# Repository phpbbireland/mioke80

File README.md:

# Moving this repo to phpbbireland/mioke  
The new repo wil correct directory structure for this project... this repo will be deleted...

# mioke80 / ayla_411
QMK Based Open Hardware Keyboard with 99 Keys and Via Support

Just another open source / open hardware ~80% keyboard...

Ref: https://hackaday.io/project/197065-mioke80-iso-99-key-80-keyboard

+ Schematic complete...  
+ Software 80% complete...  
+ QMK/VIA code tested on Blackpill 411 Dev Board (see blackpill_version)... working 11th August 2024
+ Keyboard works... Now loads in usevia.app... Needed work to get RGB and Encoder working...

My main test code is now in /blackpill_version/QMK/ayla/ayla80  

I have designed a new test board using the STM32F411RETx, it contains all the necessary keyboard electronics (except for the key switches, matrix diodes and RGB leds as these are on
the actual keyboard PCB from the first prototype). Connection between boards is via 30 pin 1.27" pitch header connector.  

Note: *kicad2* folder contains working test copy, files will be moved to **kicad** once testing complete...  

Kicad Resources:  
[https://github.com/ebastler/marbastlib](https://github.com/ebastler/marbastlib)  
[https://github.com/joe-scotto/scottokeebs](https://github.com/joe-scotto/scottokeebs)

Matrix 10X10
```
    ┌───┐   ┌───┐┌───┐┌───┬───┬───┬───┐┌───┬───┬───┬───┐┌───┬───┬───┬───┐┌───┐┌───┐┌───┐
    │0,0│   │0,1││N/A││0,2│0,3│0,4│0,5││0,6│0,7│0,8│0,9││1,0│1,1│1,2│1,3││1,4││1,5││1,6│
    └───┘   └───┘└───┘└───┴───┴───┴───┘└───┴───┴───┴───┘└───┴───┴───┴───┘└───┘└───┘└───┘
    ┌───┐   ┌───┬───┬───┬───┬───┬───┬───┬───┬───┬───┬───┬───┬───┬───────┐┌───┐┌───┐┌───┐
    │1,7│   │1,8│1,9│2,0│2,1│2,2│2,3│2,4│2,5│2,6│2,7│2,8│2,9│3,0│  3,1  ││3,2││3,3││3,4│
    ├───┤   ├───┴─┬─┴─┬─┴─┬─┴─┬─┴─┬─┴─┬─┴─┬─┴─┬─┴─┬─┴─┬─┴─┬─┴─┬─┴─┬─────┤├───┤├───┤├───┤
    │3,5│   │ 3,6 │3,7│3,8│3,9│4,0│4,1│4,2│4,3│4,4│4,5│4,6│4,7│4,8│     ││4,9││5,0││5,1│
    ├───┤   ├─────┴┬──┴┬──┴┬──┴┬──┴┬──┴┬──┴┬──┴┬──┴┬──┴┬──┴┬──┴┬──┴┐    │├───┤├───┤├───┤
    │5,2│   │ 5,3  │5,4│5,5│5,6│5,7│5,8│5,9│6,0│6,1│6,2│6,3│6,4│6,5│6.6 ││6,7││6,8││6,9│
    ├───┤   ├────┬─┴─┬─┴─┬─┴─┬─┴─┬─┴─┬─┴─┬─┴─┬─┴─┬─┴─┬─┴─┬─┴─┬─┴───┴────┤├───┤├───┤├───┤
    │7,0│   │7,1 │7,2│7,3│7,4│7,5│7,6│7,7│7,8│7,9│8,0│8,1│8,2│    8,3   ││8,4││8,5││8,6│
    ├───┤   ├────┼───┴┬──┴─┬─┴───┴───┴───┴───┴───┴──┬┴───┼───┴┬────┬────┤├───┤├───┤├───┤
    │8,7│   │8.8 │8,9 │9,1 │           9,2          │9,3 │9,4 │9,5 │9,6 ││9,7││9,8││9,9│
    └───┘   └────┴────┴────┴────────────────────────┴────┴────┴────┴────┘└───┘└───┘└───┘
```

Will add 4x3 number keypad and rotary encoder which attaches via a 5x2 ribbon cable but might need more gpio pin, another process for this version?
The Blackpill version has an endoder... 
**Note**
Some GPIO pins may change as it appears some can't be used (according to sources)...

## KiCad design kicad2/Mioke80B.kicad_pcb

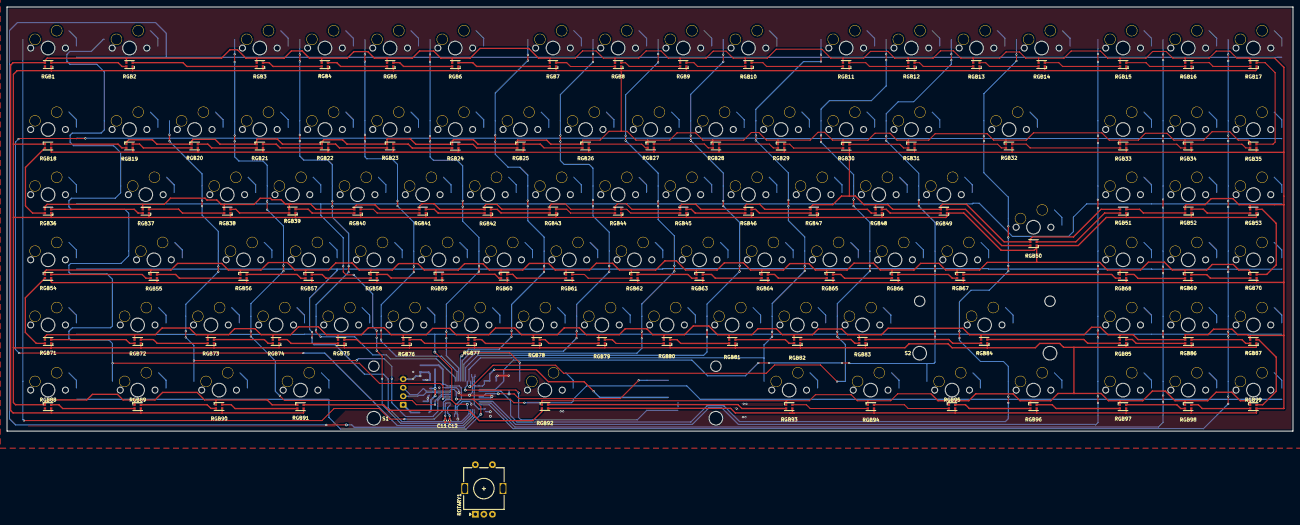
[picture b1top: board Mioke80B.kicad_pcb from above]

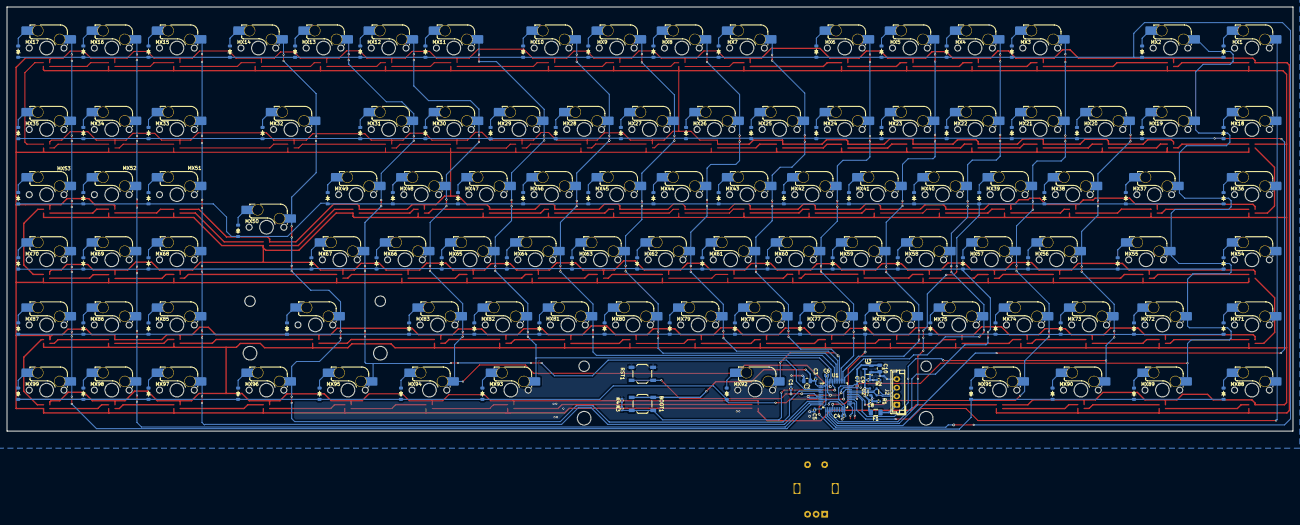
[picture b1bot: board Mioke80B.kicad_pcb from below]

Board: 2 copper layers, 376.0 x 124.0 mm, 323 parts (219 on the bottom side), 236 nets.

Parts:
BOOT1: SW_SPST; SW_SPST_TL3342
C1, C3, C4, C5, C6, C7, C8, C11, C12: 100nF; C_0402_1005Metric
C2: 47uF; C_0805_2012Metric
C9: 1uF; C_0402_1005Metric
C10: 10uF; C_0805_2012Metric
D1, D2, D3, D4, D5, D6, D7, D8, D9, D10, D11, D12, D13, D14, D15, D16, D17, D18, D19, D20, D21, D22, D23, D24, D25, D26, D27, D28, D29, D30, D31, D32, D33, D34, D35, D36, D37, D38, D39, D40, D41, D42, D43, D44, D45, D46, D47, D48, D49, D50, D51, D52, D53, D54, D55, D56, D57, D58, D59, D60, D61, D62, D63, D64, D65, D66, D67, D68, D69, D70, D71, D72, D73, D74, D75, D76, D77, D78, D79, D80, D81, D82, D83, D84, D85, D86, D87, D88, D89, D90, D91, D92, D93, D94, D95, D96, D97, D98, D99: 4148; Diode_SOD-123
F1: 500mA; Fuse_1206_3216Metric
J2: Conn_01x04_Pin; JST_EH_B4B-EH-A_1x04_P2.50mm_Vertical
MX1, MX2, MX3, MX4, MX5, MX6, MX7, MX8, MX9, MX10, MX11, MX12, MX13, MX14, MX15, MX16, MX17, MX18, MX19, MX20, MX21, MX22, MX23, MX24, MX25, MX26, MX27, MX28, MX29, MX30, MX31, MX32, MX33, MX34, MX35, MX36, MX38, MX39, MX40, MX41, MX42, MX43, MX44, MX45, MX46, MX47, MX48, MX49, MX50, MX51, MX52, MX53, MX54, MX56, MX57, MX58, MX59, MX60, MX61, MX62, MX63, MX65, MX66, MX67, MX68, MX69, MX70, MX71, MX73, MX74, MX76, MX77, MX79, MX80, MX82, MX83, MX85, MX86, MX87, MX88, MX92, MX97, MX98, MX99: MX_SW_HS; SW_MX_HS_CPG151101S11_1u
MX37: MX_SW_HS; SW_MX_HS_CPG151101S11_1.5u
MX55, MX64: MX_SW_HS; SW_MX_HS_CPG151101S11_1.75u
MX72, MX89, MX90, MX91, MX93, MX94, MX95, MX96: MX_SW_HS; SW_MX_HS_CPG151101S11_1.25u
MX75, MX78, MX81: MX_SW_HS; SW_MX_HS_1U
MX84: MX_SW_HS; SW_MX_HS_2.75U
R1, R2, R3, R4: 5.1k; R_0402_1005Metric
RGB1, RGB2, RGB3, RGB4, RGB5, RGB6, RGB7, RGB8, RGB9, RGB10, RGB11, RGB12, RGB13, RGB14, RGB15, RGB16, RGB17, RGB18, RGB19, RGB20, RGB21, RGB22, RGB23, RGB24, RGB25, RGB26, RGB27, RGB28, RGB29, RGB30, RGB31, RGB32, RGB33, RGB34, RGB35, RGB36, RGB37, RGB38, RGB39, RGB40, RGB41, RGB42, RGB43, RGB44, RGB45, RGB46, RGB47, RGB48, RGB49, RGB50, RGB51, RGB52, RGB53, RGB54, RGB55, RGB56, RGB57, RGB58, RGB59, RGB60, RGB61, RGB62, RGB63, RGB64, RGB65, RGB66, RGB67, RGB68, RGB69, RGB70, RGB71, RGB72, RGB73, RGB74, RGB75, RGB76, RGB77, RGB78, RGB79, RGB80, RGB81, RGB82, RGB83, RGB84, RGB85, RGB86, RGB87, RGB88, RGB89, RGB90, RGB91, RGB92, RGB93, RGB94, RGB95, RGB96, RGB97, RGB98, RGB99: WS2812B; LED_WS2812B-2020_PLCC4_2.0x2.0mm
ROTARY1: Volume/RGB; RotaryEncoder_Alps_EC11E-Switch_Vertical_H20mm
RST1: SW_SPST; SW_SPST_TL3342
S1: MX_stab; Stabilizer_MX_6.25u
S2: MX_stab; Stabilizer_MX_3.00u
U1: STM32F072CBT6; LQFP-48_7x7mm_P0.5mm
U2: PRTR5V0U2X; SOT-143
U3: XC6206PxxxMR-Regulator_Linear; SOT-23

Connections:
+3V3: BOOT1.1 (A), C2.1, C3.1, C4.1, C5.1, C6.1, C7.1, C10.1, U1.1 (VBAT), U1.9 (VDDA), U1.24 (VDD), U1.36 (VDDIO2), U1.48 (VDD), U3.2 (VO)
+5V: C8.1, C9.1, F1.2, U2.4 (VCC), U3.3 (VI)
BOOT0: BOOT1.2 (B), R3.1, U1.44 (BOOT0)
COL0: MX1.1, MX18.1, MX36.1, MX54.1, MX71.1, MX88.1, U1.28 (PB15)
COL1: MX2.1, MX19.1, MX37.1, MX55.1, MX72.1, MX89.1, U1.29 (PA8)
COL2: MX20.1, MX38.1, MX56.1, MX73.1, MX90.1, U1.30 (PA9)
COL3: MX3.1, MX21.1, MX39.1, MX57.1, MX74.1, MX91.1, U1.31 (PA10)
COL4: MX4.1, MX22.1, MX40.1, MX58.1, MX75.1, U1.37 (PA14)
COL5: MX5.1, MX23.1, MX41.1, MX59.1, MX76.1, U1.38 (PA15)
COL6: MX6.1, MX24.1, MX42.1, MX60.1, MX77.1, U1.39 (PB3)
COL7: MX7.1, MX25.1, MX43.1, MX61.1, MX78.1, MX92.1, U1.40 (PB4)
COL8: MX8.1, MX26.1, MX44.1, MX62.1, MX79.1, U1.41 (PB5)
COL9: MX9.1, MX27.1, MX45.1, MX63.1, MX80.1, U1.42 (PB6)
COL10: MX10.1, MX28.1, MX46.1, MX64.1, MX81.1, U1.43 (PB7)
COL11: MX11.1, MX29.1, MX47.1, MX65.1, MX82.1, MX93.1, U1.45 (PB8)
COL12: MX12.1, MX30.1, MX48.1, MX66.1, MX83.1, MX94.1, U1.46 (PB9)
COL13: MX13.1, MX31.1, MX49.1, MX67.1, MX95.1, U1.3 (PC14)
COL14: MX14.1, MX32.1, MX50.1, MX84.1, MX96.1, U1.4 (PC15)
COL15: MX15.1, MX33.1, MX51.1, MX68.1, MX85.1, MX97.1, U1.10 (PA0)
COL16: MX16.1, MX34.1, MX52.1, MX69.1, MX86.1, MX98.1, U1.11 (PA1)
COL17: MX17.1, MX35.1, MX53.1, MX70.1, MX87.1, MX99.1, U1.12 (PA2)
D+: J2.3, U1.33 (PA12), U2.3 (I/O2)
D-: J2.2, U1.32 (PA11), U2.2 (I/O1)
GND: C1.2, C2.2, C3.2, C4.2, C5.2, C6.2, C7.2, C8.2, C9.2, C10.2, C11.2, C12.2, J2.4, R1.1, R2.2, R4.2, ROTARY1.C, RST1.2 (B), U1.8 (VSSA), U1.23 (VSS), U1.35 (VSS), U1.47 (VSS), U2.1 (GND), U3.1 (GND)
NRST: C1.1, RST1.1 (A), U1.7 (NRST)
unnamed: D1.2 (A), MX1.2
unnamed: D2.2 (A), MX2.2
unnamed: D3.2 (A), MX3.2
unnamed: D4.2 (A), MX4.2
unnamed: D5.2 (A), MX5.2
unnamed: D6.2 (A), MX6.2
unnamed: D7.2 (A), MX7.2
unnamed: D8.2 (A), MX8.2
unnamed: D9.2 (A), MX9.2
unnamed: D10.2 (A), MX10.2
unnamed: D11.2 (A), MX11.2
unnamed: D12.2 (A), MX12.2
unnamed: D13.2 (A), MX13.2
unnamed: D14.2 (A), MX14.2
unnamed: D15.2 (A), MX15.2
unnamed: D16.2 (A), MX16.2
unnamed: D17.2 (A), MX17.2
unnamed: D18.2 (A), MX18.2
unnamed: D19.2 (A), MX19.2
unnamed: D20.2 (A), MX20.2
unnamed: D21.2 (A), MX21.2
unnamed: D22.2 (A), MX22.2
unnamed: D23.2 (A), MX23.2
unnamed: D24.2 (A), MX24.2
unnamed: D25.2 (A), MX25.2
unnamed: D26.2 (A), MX26.2
unnamed: D27.2 (A), MX27.2
unnamed: D28.2 (A), MX28.2
unnamed: D29.2 (A), MX29.2
unnamed: D30.2 (A), MX30.2
unnamed: D31.2 (A), MX31.2
unnamed: D32.2 (A), MX32.2
unnamed: D33.2 (A), MX33.2
unnamed: D34.2 (A), MX34.2
unnamed: D35.2 (A), MX35.2
unnamed: D36.2 (A), MX36.2
unnamed: D37.2 (A), MX37.2
unnamed: D38.2 (A), MX38.2
unnamed: D39.2 (A), MX39.2
unnamed: D40.2 (A), MX40.2
unnamed: D41.2 (A), MX41.2
unnamed: D42.2 (A), MX42.2
unnamed: D43.2 (A), MX43.2
unnamed: D44.2 (A), MX44.2
unnamed: D45.2 (A), MX45.2
unnamed: D46.2 (A), MX46.2
unnamed: D47.2 (A), MX47.2
unnamed: D48.2 (A), MX48.2
unnamed: D49.2 (A), MX49.2
unnamed: D50.2 (A), MX50.2
unnamed: D51.2 (A), MX51.2
unnamed: D52.2 (A), MX52.2
unnamed: D53.2 (A), MX53.2
unnamed: D54.2 (A), MX54.2
unnamed: D55.2 (A), MX55.2
unnamed: D56.2 (A), MX56.2
unnamed: D57.2 (A), MX57.2
unnamed: D58.2 (A), MX58.2
unnamed: D59.2 (A), MX59.2
unnamed: D60.2 (A), MX60.2
unnamed: D61.2 (A), MX61.2
unnamed: D62.2 (A), MX62.2
unnamed: D63.2 (A), MX63.2
unnamed: D64.2 (A), MX64.2
unnamed: D65.2 (A), MX65.2
unnamed: D66.2 (A), MX66.2
unnamed: D67.2 (A), MX67.2
unnamed: D68.2 (A), MX68.2
unnamed: D69.2 (A), MX69.2
unnamed: D70.2 (A), MX70.2
unnamed: D71.2 (A), MX71.2
unnamed: D72.2 (A), MX72.2
unnamed: D73.2 (A), MX73.2
unnamed: D74.2 (A), MX74.2
unnamed: D75.2 (A), MX75.2
unnamed: D76.2 (A), MX76.2
unnamed: D77.2 (A), MX77.2
unnamed: D78.2 (A), MX78.2
unnamed: D79.2 (A), MX79.2
unnamed: D80.2 (A), MX80.2
unnamed: D81.2 (A), MX81.2
unnamed: D82.2 (A), MX82.2
unnamed: D83.2 (A), MX83.2
unnamed: D84.2 (A), MX84.2
unnamed: D85.2 (A), MX85.2
unnamed: D86.2 (A), MX86.2
unnamed: D87.2 (A), MX87.2
unnamed: D88.2 (A), MX88.2
unnamed: D89.2 (A), MX89.2
unnamed: D90.2 (A), MX90.2
unnamed: D91.2 (A), MX91.2
unnamed: D92.2 (A), MX92.2
unnamed: D93.2 (A), MX93.2
unnamed: D94.2 (A), MX94.2
unnamed: D95.2 (A), MX95.2
unnamed: D96.2 (A), MX96.2
unnamed: D97.2 (A), MX97.2
unnamed: D98.2 (A), MX98.2
unnamed: D99.2 (A), MX99.2
unnamed: R3.2, R4.1
unnamed: RGB1.2 (DOUT), RGB2.4 (DIN)
unnamed: RGB1.1 (VDD), RGB2.1 (VDD), RGB3.1 (VDD), RGB4.1 (VDD), RGB5.1 (VDD), RGB6.1 (VDD), RGB7.1 (VDD), RGB8.1 (VDD), RGB9.1 (VDD), RGB10.1 (VDD), RGB11.1 (VDD), RGB12.1 (VDD), RGB13.1 (VDD), RGB14.1 (VDD), RGB15.1 (VDD), RGB16.1 (VDD), RGB17.1 (VDD), RGB18.1 (VDD), RGB19.1 (VDD), RGB20.1 (VDD), RGB21.1 (VDD), RGB22.1 (VDD), RGB23.1 (VDD), RGB24.1 (VDD), RGB25.1 (VDD), RGB26.1 (VDD), RGB27.1 (VDD), RGB28.1 (VDD), RGB29.1 (VDD), RGB30.1 (VDD), RGB31.1 (VDD), RGB32.1 (VDD), RGB33.1 (VDD), RGB34.1 (VDD), RGB35.1 (VDD), RGB36.1 (VDD), RGB37.1 (VDD), RGB38.1 (VDD), RGB39.1 (VDD), RGB40.1 (VDD), RGB41.1 (VDD), RGB42.1 (VDD), RGB43.1 (VDD), RGB44.1 (VDD), RGB45.1 (VDD), RGB46.1 (VDD), RGB47.1 (VDD), RGB48.1 (VDD), RGB49.1 (VDD), RGB50.1 (VDD), RGB51.1 (VDD), RGB52.1 (VDD), RGB53.1 (VDD), RGB54.1 (VDD), RGB55.1 (VDD), RGB56.1 (VDD), RGB57.1 (VDD), RGB58.1 (VDD), RGB59.1 (VDD), RGB60.1 (VDD), RGB61.1 (VDD), RGB62.1 (VDD), RGB63.1 (VDD), RGB64.1 (VDD), RGB65.1 (VDD), RGB66.1 (VDD), RGB67.1 (VDD), RGB68.1 (VDD), RGB69.1 (VDD), RGB70.1 (VDD), RGB71.1 (VDD), RGB72.1 (VDD), RGB73.1 (VDD), RGB74.1 (VDD), RGB75.1 (VDD), RGB76.1 (VDD), RGB77.1 (VDD), RGB78.1 (VDD), RGB79.1 (VDD), RGB80.1 (VDD), RGB81.1 (VDD), RGB82.1 (VDD), RGB83.1 (VDD), RGB84.1 (VDD), RGB85.1 (VDD), RGB86.1 (VDD), RGB87.1 (VDD), RGB88.1 (VDD), RGB89.1 (VDD), RGB90.1 (VDD), RGB91.1 (VDD), RGB92.1 (VDD), RGB93.1 (VDD), RGB94.1 (VDD), RGB95.1 (VDD), RGB96.1 (VDD), RGB97.1 (VDD), RGB98.1 (VDD), RGB99.1 (VDD)
unnamed: RGB1.3 (VSS), RGB2.3 (VSS), RGB3.3 (VSS), RGB4.3 (VSS), RGB5.3 (VSS), RGB6.3 (VSS), RGB7.3 (VSS), RGB8.3 (VSS), RGB9.3 (VSS), RGB10.3 (VSS), RGB11.3 (VSS), RGB12.3 (VSS), RGB13.3 (VSS), RGB14.3 (VSS), RGB15.3 (VSS), RGB16.3 (VSS), RGB17.3 (VSS), RGB18.3 (VSS), RGB19.3 (VSS), RGB20.3 (VSS), RGB21.3 (VSS), RGB22.3 (VSS), RGB23.3 (VSS), RGB24.3 (VSS), RGB25.3 (VSS), RGB26.3 (VSS), RGB27.3 (VSS), RGB28.3 (VSS), RGB29.3 (VSS), RGB30.3 (VSS), RGB31.3 (VSS), RGB32.3 (VSS), RGB33.3 (VSS), RGB34.3 (VSS), RGB35.3 (VSS), RGB36.3 (VSS), RGB37.3 (VSS), RGB38.3 (VSS), RGB39.3 (VSS), RGB40.3 (VSS), RGB41.3 (VSS), RGB42.3 (VSS), RGB43.3 (VSS), RGB44.3 (VSS), RGB45.3 (VSS), RGB46.3 (VSS), RGB47.3 (VSS), RGB48.3 (VSS), RGB49.3 (VSS), RGB50.3 (VSS), RGB51.3 (VSS), RGB52.3 (VSS), RGB53.3 (VSS), RGB54.3 (VSS), RGB55.3 (VSS), RGB56.3 (VSS), RGB57.3 (VSS), RGB58.3 (VSS), RGB59.3 (VSS), RGB60.3 (VSS), RGB61.3 (VSS), RGB62.3 (VSS), RGB63.3 (VSS), RGB64.3 (VSS), RGB65.3 (VSS), RGB66.3 (VSS), RGB67.3 (VSS), RGB68.3 (VSS), RGB69.3 (VSS), RGB70.3 (VSS), RGB71.3 (VSS), RGB72.3 (VSS), RGB73.3 (VSS), RGB74.3 (VSS), RGB75.3 (VSS), RGB76.3 (VSS), RGB77.3 (VSS), RGB78.3 (VSS), RGB79.3 (VSS), RGB80.3 (VSS), RGB81.3 (VSS), RGB82.3 (VSS), RGB83.3 (VSS), RGB84.3 (VSS), RGB85.3 (VSS), RGB86.3 (VSS), RGB87.3 (VSS), RGB88.3 (VSS), RGB89.3 (VSS), RGB90.3 (VSS), RGB91.3 (VSS), RGB92.3 (VSS), RGB93.3 (VSS), RGB94.3 (VSS), RGB95.3 (VSS), RGB96.3 (VSS), RGB97.3 (VSS), RGB98.3 (VSS), RGB99.3 (VSS)
unnamed: RGB2.2 (DOUT), RGB3.4 (DIN)
unnamed: RGB3.2 (DOUT), RGB4.4 (DIN)
unnamed: RGB4.2 (DOUT), RGB5.4 (DIN)
unnamed: RGB5.2 (DOUT), RGB6.4 (DIN)
unnamed: RGB6.2 (DOUT), RGB7.4 (DIN)
unnamed: RGB7.2 (DOUT), RGB8.4 (DIN)
unnamed: RGB8.2 (DOUT), RGB9.4 (DIN)
unnamed: RGB9.2 (DOUT), RGB10.4 (DIN)
unnamed: RGB10.2 (DOUT), RGB11.4 (DIN)
unnamed: RGB11.2 (DOUT), RGB12.4 (DIN)
unnamed: RGB12.2 (DOUT), RGB13.4 (DIN)
unnamed: RGB13.2 (DOUT), RGB14.4 (DIN)
unnamed: RGB14.2 (DOUT), RGB15.4 (DIN)
unnamed: RGB15.2 (DOUT), RGB16.4 (DIN)
unnamed: RGB16.2 (DOUT), RGB17.4 (DIN)
unnamed: RGB17.2 (DOUT), RGB35.4 (DIN)
unnamed: RGB18.4 (DIN), RGB19.2 (DOUT)
unnamed: RGB18.2 (DOUT), RGB36.4 (DIN)
unnamed: RGB19.4 (DIN), RGB20.2 (DOUT)
unnamed: RGB20.4 (DIN), RGB21.2 (DOUT)
unnamed: RGB21.4 (DIN), RGB22.2 (DOUT)
unnamed: RGB22.4 (DIN), RGB23.2 (DOUT)
unnamed: RGB23.4 (DIN), RGB24.2 (DOUT)
unnamed: RGB24.4 (DIN), RGB25.2 (DOUT)
unnamed: RGB25.4 (DIN), RGB26.2 (DOUT)
unnamed: RGB26.4 (DIN), RGB27.2 (DOUT)
unnamed: RGB27.4 (DIN), RGB28.2 (DOUT)
unnamed: RGB28.4 (DIN), RGB29.2 (DOUT)
unnamed: RGB29.4 (DIN), RGB30.2 (DOUT)
unnamed: RGB30.4 (DIN), RGB31.2 (DOUT)
unnamed: RGB31.4 (DIN), RGB32.2 (DOUT)
unnamed: RGB32.4 (DIN), RGB33.2 (DOUT)
unnamed: RGB33.4 (DIN), RGB34.2 (DOUT)
unnamed: RGB34.4 (DIN), RGB35.2 (DOUT)
unnamed: RGB36.2 (DOUT), RGB37.4 (DIN)
unnamed: RGB37.2 (DOUT), RGB38.4 (DIN)
unnamed: RGB38.2 (DOUT), RGB39.4 (DIN)
unnamed: RGB39.2 (DOUT), RGB40.4 (DIN)
unnamed: RGB40.2 (DOUT), RGB41.4 (DIN)
unnamed: RGB41.2 (DOUT), RGB42.4 (DIN)
unnamed: RGB42.2 (DOUT), RGB43.4 (DIN)
unnamed: RGB43.2 (DOUT), RGB44.4 (DIN)
unnamed: RGB44.2 (DOUT), RGB45.4 (DIN)
unnamed: RGB45.2 (DOUT), RGB46.4 (DIN)
unnamed: RGB46.2 (DOUT), RGB47.4 (DIN)
unnamed: RGB47.2 (DOUT), RGB48.4 (DIN)
unnamed: RGB48.2 (DOUT), RGB49.4 (DIN)
unnamed: RGB49.2 (DOUT), RGB50.4 (DIN)
unnamed: RGB50.2 (DOUT), RGB51.4 (DIN)
unnamed: RGB51.2 (DOUT), RGB52.4 (DIN)
unnamed: RGB52.2 (DOUT), RGB53.4 (DIN)
unnamed: RGB53.2 (DOUT), RGB70.4 (DIN)
unnamed: RGB54.4 (DIN), RGB55.2 (DOUT)
unnamed: RGB54.2 (DOUT), RGB71.4 (DIN)
unnamed: RGB55.4 (DIN), RGB56.2 (DOUT)
unnamed: RGB56.4 (DIN), RGB57.2 (DOUT)
unnamed: RGB57.4 (DIN), RGB58.2 (DOUT)
unnamed: RGB58.4 (DIN), RGB59.2 (DOUT)
unnamed: RGB59.4 (DIN), RGB60.2 (DOUT)
unnamed: RGB60.4 (DIN), RGB61.2 (DOUT)
unnamed: RGB61.4 (DIN), RGB62.2 (DOUT)
unnamed: RGB62.4 (DIN), RGB63.2 (DOUT)
unnamed: RGB63.4 (DIN), RGB64.2 (DOUT)
unnamed: RGB64.4 (DIN), RGB65.2 (DOUT)
unnamed: RGB65.4 (DIN), RGB66.2 (DOUT)
unnamed: RGB66.4 (DIN), RGB67.2 (DOUT)
unnamed: RGB67.4 (DIN), RGB68.2 (DOUT)
unnamed: RGB68.4 (DIN), RGB69.2 (DOUT)
unnamed: RGB69.4 (DIN), RGB70.2 (DOUT)
unnamed: RGB71.2 (DOUT), RGB72.4 (DIN)
unnamed: RGB72.2 (DOUT), RGB73.4 (DIN)
unnamed: RGB73.2 (DOUT), RGB74.4 (DIN)
unnamed: RGB74.2 (DOUT), RGB75.4 (DIN)
unnamed: RGB75.2 (DOUT), RGB76.4 (DIN)
unnamed: RGB76.2 (DOUT), RGB77.4 (DIN)
unnamed: RGB77.2 (DOUT), RGB78.4 (DIN)
unnamed: RGB78.2 (DOUT), RGB79.4 (DIN)
unnamed: RGB79.2 (DOUT), RGB80.4 (DIN)
unnamed: RGB80.2 (DOUT), RGB81.4 (DIN)
unnamed: RGB81.2 (DOUT), RGB82.4 (DIN)
unnamed: RGB82.2 (DOUT), RGB83.4 (DIN)
unnamed: RGB83.2 (DOUT), RGB84.4 (DIN)
unnamed: RGB84.2 (DOUT), RGB85.4 (DIN)
unnamed: RGB85.2 (DOUT), RGB86.4 (DIN)
unnamed: RGB86.2 (DOUT), RGB87.4 (DIN)
unnamed: RGB87.2 (DOUT), RGB99.4 (DIN)
unnamed: RGB88.4 (DIN), RGB89.2 (DOUT)
unnamed: RGB89.4 (DIN), RGB90.2 (DOUT)
unnamed: RGB90.4 (DIN), RGB91.2 (DOUT)
unnamed: RGB91.4 (DIN), RGB92.2 (DOUT)
unnamed: RGB92.4 (DIN), RGB93.2 (DOUT)
unnamed: RGB93.4 (DIN), RGB94.2 (DOUT)
unnamed: RGB94.4 (DIN), RGB95.2 (DOUT)
unnamed: RGB95.4 (DIN), RGB96.2 (DOUT)
unnamed: RGB96.4 (DIN), RGB97.2 (DOUT)
unnamed: RGB97.4 (DIN), RGB98.2 (DOUT)
unnamed: RGB98.4 (DIN), RGB99.2 (DOUT)
unnamed: ROTARY1.S1, U1.21 (PB10)
unnamed: ROTARY1.S2, U1.22 (PB11)
unnamed: C12.1, ROTARY1.B, U1.25 (PB12)
unnamed: C11.1, ROTARY1.A, U1.26 (PB13)
ROW0: D1.1 (K), D2.1 (K), D3.1 (K), D4.1 (K), D5.1 (K), D6.1 (K), D7.1 (K), D8.1 (K), D9.1 (K), D10.1 (K), D11.1 (K), D12.1 (K), D13.1 (K), D14.1 (K), D15.1 (K), D16.1 (K), D17.1 (K), U1.13 (PA3)
ROW1: D18.1 (K), D19.1 (K), D20.1 (K), D21.1 (K), D22.1 (K), D23.1 (K), D24.1 (K), D25.1 (K), D26.1 (K), D27.1 (K), D28.1 (K), D29.1 (K), D30.1 (K), D31.1 (K), D32.1 (K), D33.1 (K), D34.1 (K), D35.1 (K), U1.14 (PA4)
ROW2: D36.1 (K), D37.1 (K), D38.1 (K), D39.1 (K), D40.1 (K), D41.1 (K), D42.1 (K), D43.1 (K), D44.1 (K), D45.1 (K), D46.1 (K), D47.1 (K), D48.1 (K), D49.1 (K), D50.1 (K), D51.1 (K), D52.1 (K), D53.1 (K), U1.15 (PA5)
ROW3: D54.1 (K), D55.1 (K), D56.1 (K), D57.1 (K), D58.1 (K), D59.1 (K), D60.1 (K), D61.1 (K), D62.1 (K), D63.1 (K), D64.1 (K), D65.1 (K), D66.1 (K), D67.1 (K), D68.1 (K), D69.1 (K), D70.1 (K), U1.16 (PA6)
ROW4: D71.1 (K), D72.1 (K), D73.1 (K), D74.1 (K), D75.1 (K), D76.1 (K), D77.1 (K), D78.1 (K), D79.1 (K), D80.1 (K), D81.1 (K), D82.1 (K), D83.1 (K), D84.1 (K), D85.1 (K), D86.1 (K), D87.1 (K), U1.17 (PA7)
ROW5: D88.1 (K), D89.1 (K), D90.1 (K), D91.1 (K), D92.1 (K), D93.1 (K), D94.1 (K), D95.1 (K), D96.1 (K), D97.1 (K), D98.1 (K), D99.1 (K), U1.34 (PA13)
VBUS: F1.1, J2.1

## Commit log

2024-07-25 Create README.md
    Creation...
2024-07-25 Add images
2024-07-25 More images
2024-07-25 Kicad Files...
2024-07-27 working active version
2024-07-27 Update README.md
    general update
2024-07-31 new files
2024-07-31 layout file store
2024-08-12 Create config.h
    Added qmk config.h
2024-08-12 Update keyboard.json
    removed comments... json doesn't support comments?
2024-08-15 Add files via upload
    Image of edited marbastlib-mx:SW_MX_HS_CPG151101S11_xxx to include graphics to align the RGB led ...
2024-08-18 Create README.md
    For blackpill version
2024-08-18 Create placeholder
2024-08-18 Added blackpill board image
2024-08-18 blackpill board
2024-08-18 Delete blackpill_version/images/Blackpill_Pinout2.jpg
    Wrong image uploaded
2024-08-18 Schematic for plackpill
2024-08-22 Add files via upload
    New, updated version
2024-08-22 Add files via upload
    4 Layer board
2024-08-22 Add files via upload
    3D Image
2024-08-22 Create placeholder
    temp file
2024-08-22 Add files via upload
    Files with 10x10 matrix layout (for four layer board)
2024-08-22 Create keyboard_layout.json
    keyboard_layout.com file
2024-08-23 keyboard_layout.json for keyboard_layout.com
2024-08-23 Update config.h
    Changed matrix to 10x10
2024-08-23 Update keyboard.json
    Changed cols/rows pin assignment
2024-08-23 Update keyboard.json
    Removed comments
2024-08-23 Update keymap.c
    Update for new col/row
2024-08-23 Update keymap.c
    Corrected for missing key
2024-08-23 Add files via upload
    Colour...
2024-08-23 Update keyboard.json
    It's Euro ready ;)
2024-08-25 Update keymap.c
    temp change
2024-08-25 Add files via upload
    Thanks to REDDITz3r0 for the help...
2024-08-25 Delete blackpill_version/QMK/ayla_411/via directory
    wrong place
2024-08-25 Add files via upload
    information I need
2024-08-25 Add files via upload
    update pcb
2024-08-25 Add files via upload
    Required for plugin
2024-08-25 Delete blackpill_version/images/schematic_10x10_matrix.png
    updated...
2024-08-25 Add files via upload
    Update with changes
2024-08-25 Delete blackpill_version/images/schematic_411.png
    updated again
2024-08-26 Update keyboard.json
    Added labels, removed comments (don't think comments are permitted in json).
2024-09-11 Update keymap.c
    Some fixes after building prototype
2024-09-11 Update keyboard.info
    update shift sizes
2024-09-11 Update keyboard_layout.json
    moved a key updated shift sizes
2024-09-11 Add files via upload
    Corrected for new layout
2024-09-11 Update keymap.c
    moved rgb keys around
2024-09-12 Update README.md
    moved \ back slash
2024-10-07 Update keymap.c
    Minor changes...
2024-10-07 Create keymap.c
    moving to default location
2024-10-07 Add files via upload
    Default files ayla80
2024-10-07 Update compile info
    compile example text
2024-10-07 Create README.md
    Changing to default ayla keyboard code/directories
2024-10-28 Add files via upload
    Added via.json for reference
2024-10-31 Create via.json
    Added Chrome test file
2024-11-02 Delete blackpill_version/QMK/ayla/ayla80/mcuconf.h
    Not required for blackpill
2024-11-02 Delete blackpill_version/QMK/ayla/ayla80/keymap.c
    Not required... chasing shadows...
2024-11-02 Delete blackpill_version/QMK/ayla/ayla80/ayla80.json
    Not required... chasing shadows...
2024-11-02 Update keyboard.json
    latest updates compiling and working in usevia.app
2024-11-02 Delete blackpill_version/QMK/ayla/ayla80/halconf.h
    Not required...
2024-11-02 Create ayla_keyboard.layout.json
    Moved, it's only for reference...
2024-11-02 Update ayla_keyboard.layout.json
    move
2024-11-02 Delete blackpill_version/QMK/ayla/ayla80/ayla_keyboard.layout.json
    Moved, file is for reference only
2024-11-02 Update rules.mk
    Just the basics required for now...
2024-11-02 Update README.md
    General updates
2024-11-02 Update README.md
    Minor update
2024-11-02 Update keyboard.json
    changed pid
2024-11-04 Create info.json
    This is default kb
2024-11-04 Add files via upload
    ayla80 is default
2024-11-04 Add files via upload
    Current attempts
2024-11-04 Create keyboard_layout.json
    Moved temp file to store
2024-11-04 Delete blackpill_version/QMK/keyboard_layout.json
    moved to store
